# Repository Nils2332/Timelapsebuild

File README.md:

# 3 Axis Camera Motion System

A simple 4 digit stopwatch triggered by 2 remote Buttons<br />

<br />
Demo of Moving System<br />
<br />
Motion-System<br />
<br />
Remote-Controller<br />
## Built With
Motor Driver Board with STM32 Microcontroller and TMC2130 Stepper-Driver.<br />
Remote-Controller with STM32 $\muC
$ Touchscreen and two Joysticks.<br />
Both connected remotly via nRF905 wireless Chip on 868 MHz band. <br />

## License

This project is licensed under the MIT License

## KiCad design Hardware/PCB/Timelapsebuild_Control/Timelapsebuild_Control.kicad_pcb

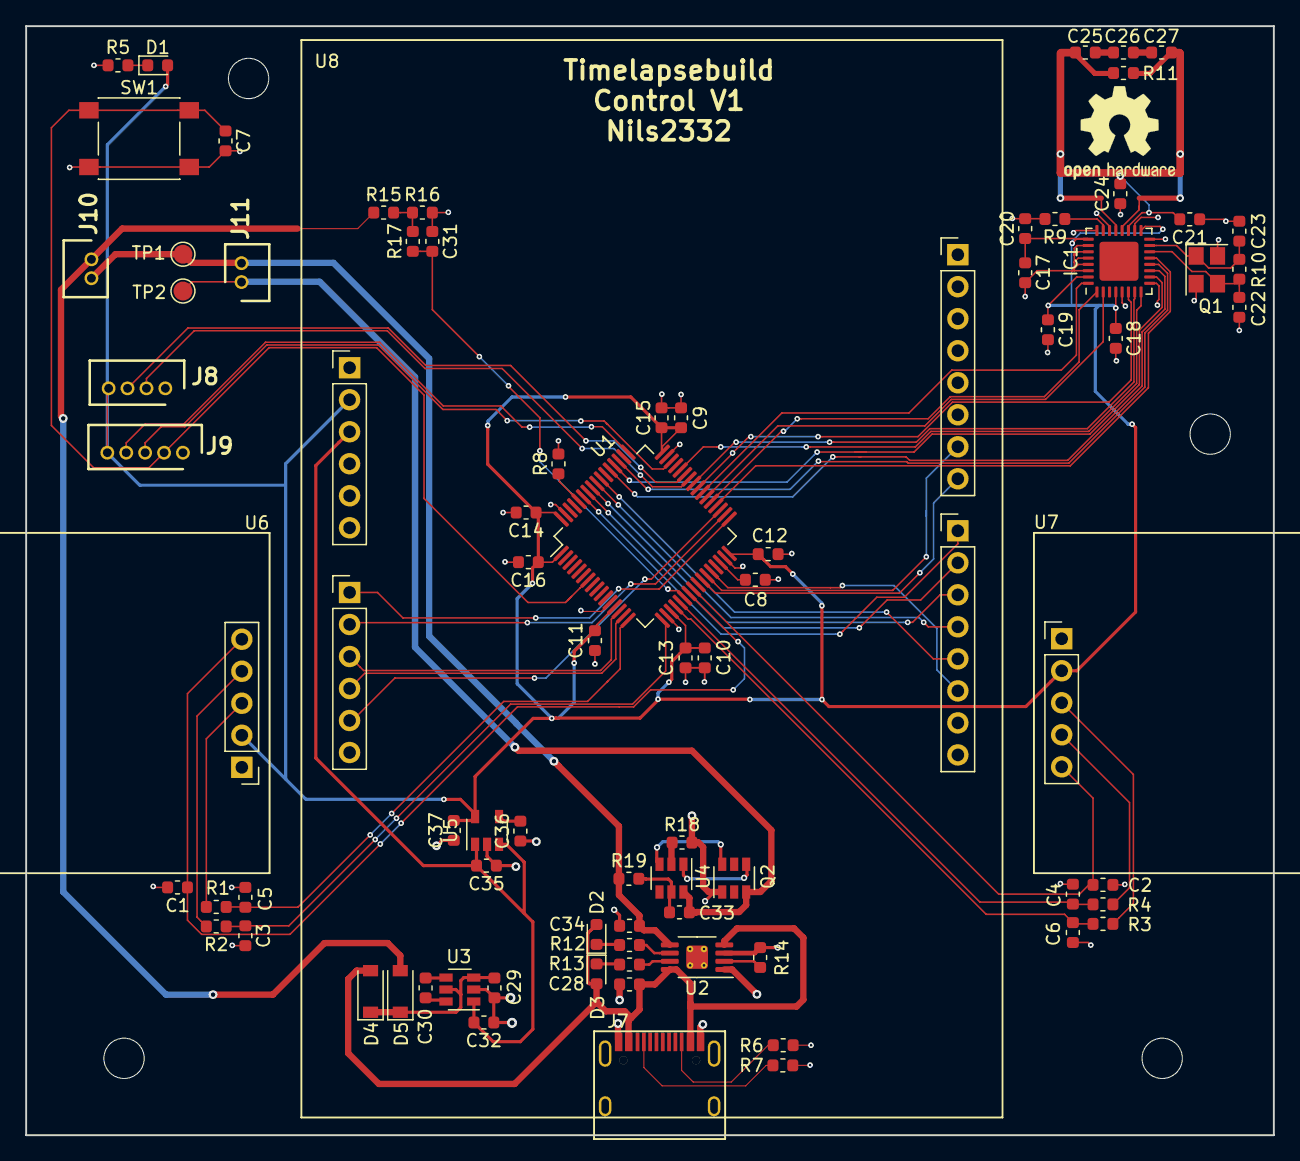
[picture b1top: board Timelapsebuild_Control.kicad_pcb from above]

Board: 2 copper layers, 99.0 x 88.0 mm, 80 parts (0 on the bottom side), 71 nets.

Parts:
C1, C2, C7, C9, C10, C11, C12, C13, C14, C15, C28, C33: 100n; C_0603_1608Metric
C3, C4, C5, C6, C36: 10n; C_0603_1608Metric
C8, C16: 4.7u; C_0603_1608Metric
C17, C18, C24: 33pF; C_0603_1608Metric
C19, C31: 10nF; C_0603_1608Metric
C20: 4.7uF; C_0603_1608Metric
C21: 3.3n; C_0603_1608Metric
C22, C23: 22pF; C_0603_1608Metric
C25: 5.6pF; C_0603_1608Metric
C26: 4.7pF; C_0603_1608Metric
C27: 3.9pF; C_0603_1608Metric
C29, C30, C32, C34: 10uF; C_0603_1608Metric
C35, C37: 1u; C_0603_1608Metric
D1, D2, D3: LED; LED_0603_1608Metric
D4, D5: 1N5819; D_SOD-123
IC1: nRF905; QFN-32-1EP_5x5mm_P0.5mm_EP3.1x3.1mm
J7: USB_C_Receptacle_USB2.0; USB_C_SIMPLE
J8: UART; JST_ZH_B4B_1x04_P1.5mm
J9: ST-Link; JST_ZH_B5B_1x05_P1.5mm
J10: PWR_Con; JST_ZH_B2B_1x02_P1.5mm
J11: Bat Con; JST_ZH_B2B_1x02_P1.5mm
Q1: X322516MRB4SI; Crystal_SMD_3225-4Pin_3.2x2.5mm
Q2: FS8205; SOT-23-6
R1, R2, R3, R4, R8, R17: 10k; R_0603_1608Metric
R5, R12, R13, R18: 1k; R_0603_1608Metric
R6, R7: 5k1; R_0603_1608Metric
R9: 22k; R_0603_1608Metric
R10: 1M; R_0603_1608Metric
R11: 18k; R_0603_1608Metric
R14: 1.2k; R_0603_1608Metric
R15: 400k; R_0603_1608Metric
R16: 100k; R_0603_1608Metric
R19: 100; R_0603_1608Metric
SW1: SW_DIP_x01; SW_SPST_PTS645
TP1, TP2: TestPoint; TestPoint_Pad_D1.5mm
U1: STM32F401RETx; LQFP-64_10x10mm_P0.5mm
U2: TP4056; MSOP-8-1EP_3x3mm_P0.65mm_EP1.73x1.85mm_ThermalVias
U3: HX4004A; SOT-23-6
U4: DW01A; SOT-23-6
U5: SGM2019-3.3YN; SOT-23-5
U6, U7: Joycon
U8: Kuman3.5T-Screen; Kuman 3.5 Display

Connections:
+3V3: C9.1, C10.1, C11.1, C12.1, C13.1, C14.1, C15.1, C16.1, C17.1, C18.1, C19.1, C20.1, C37.2, D1.2, IC1.4, IC1.17, IC1.25, IC1.31, J8.4, J9.5, U1.1, U1.13, U1.19, U1.32, U1.48, U1.64, U5.5, U6.2, U7.2, U8.24
+5V: C32.2, C35.2, U3.1, U5.1, U5.3, U8.25
+5VA: C28.1, D2.2, D3.2, D4.2, J7.A4, J7.A9, J7.B4, J7.B9, U2.4, U2.8
+BATT: C34.1, J10.2, J11.2, R19.1, TP1.1, U2.5
-BATT: C33.2, J11.1, Q2.3, TP2.1, U4.6
/Joycon1-1: C5.1, R1.1, U1.16
/Joycon1-2: C3.1, R2.1, U1.17
/Joycon1-But: C1.1, U1.23, U6.5
/Joycon2-1: C6.1, R3.1, U1.20
/Joycon2-2: C4.1, R4.1, U1.21
/Joycon2-But: C2.1, U1.24, U7.5
/LCD_CS: U1.15, U8.20
/LCD_D0: U1.26, U8.8
/LCD_D1: U1.27, U8.7
/LCD_D2: U1.28, U8.14
/LCD_D3: U1.55, U8.13
/LCD_D4: U1.56, U8.12
/LCD_D5: U1.57, U8.11
/LCD_D6: U1.58, U8.10
/LCD_D7: U1.59, U8.9
/LCD_RD: U1.33, U8.17
/LCD_RS: U1.14, U8.19
/LCD_RST: U1.35, U8.21
/LCD_WR: U1.34, U8.18
/NRST: C7.1, J9.2, SW1.1, U1.7
/SWCLK: J9.4, U1.49
/SWDIO: J9.3, U1.46
/USART1_RX: J8.3, U1.43
/USART1_TX: J8.2, U1.42
Bat_V: C31.2, R17.1, U1.22
CSN: IC1.13, U1.36
DR: IC1.8, U1.44
GND: C1.2, C2.2, C3.2, C4.2, C5.2, C6.2, C7.2, C8.2, C9.2, C10.2, C11.2, C12.2, C13.2, C14.2, C15.2, C16.2, C17.2, C18.2, C19.2, C20.2, C21.1, C22.1, C23.1, C24.1, C28.2, C29.1, C31.1, C32.1, C34.2, C35.1, C36.1, C37.1, IC1.5, IC1.9, IC1.16, IC1.18, IC1.22, IC1.24, IC1.26, IC1.27, IC1.28, IC1.29, IC1.30, J7.A1, J7.A12, J7.B1, J7.B12, J7.S1, J8.1, J9.1, Q1.2, Q1.4, Q2.1, R5.1, R6.2, R7.2, R8.2, R9.2, R14.2, R16.2, R18.2, SW1.2, U1.12, U1.18, U1.31, U1.47, U1.63, U2.1, U2.3, U3.2, U5.2, U6.1, U7.1, U8.26, U8.27
MISO: IC1.10, U1.52
MOSI: IC1.11, U1.53
unnamed: C8.1, U1.30
unnamed: C21.2, C24.2, C25.2, C27.1, IC1.19, IC1.20, IC1.21, R11.1, R11.2
unnamed: C22.2, IC1.14, Q1.3, R10.1
unnamed: C23.2, IC1.15, Q1.1, R10.2
unnamed: C25.1, C26.2
unnamed: C26.1, C27.2
unnamed: C29.2, D4.1, D5.1, U3.3, U3.5
unnamed: C30.1, U3.6
unnamed: C30.2, U3.4
unnamed: C33.1, R19.2, U4.5
unnamed: C36.2, U5.4
unnamed: D1.1, R5.2
unnamed: D2.1, R12.2
unnamed: D3.1, R13.2
unnamed: D5.2, J10.1, R15.1
unnamed: IC1.23, R9.1
unnamed: J7.A5, R7.1
unnamed: J7.B5, R6.1
unnamed: Q2.4, U4.1
unnamed: Q2.6, U4.3
unnamed: R1.2, U6.3
unnamed: R2.2, U6.4
unnamed: R3.2, U7.3
unnamed: R4.2, U7.4
unnamed: R8.1, U1.60
unnamed: R12.1, U2.6
unnamed: R13.1, U2.7
unnamed: R14.1, U2.2
unnamed: R15.2, R16.1, R17.2
unnamed: R18.1, U4.2
PWRUP: IC1.2, U1.38
RF_AM: IC1.7, U1.41
RF_CD: IC1.6, U1.40
SCK: IC1.12, U1.51
TRX_CE: IC1.1, U1.37
TX_EN: IC1.32, U1.39

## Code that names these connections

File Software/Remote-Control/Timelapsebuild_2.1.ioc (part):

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Mcu.Name=STM32F401R(D-E)Tx
Mcu.Package=LQFP64
Mcu.UserName=STM32F401RETx
PA0-WKUP.GPIOParameters=GPIO_PuPd,GPIO_Label
PA0-WKUP.GPIO_Label=LCD_CD
PA0-WKUP.GPIO_PuPd=GPIO_PULLUP
PA0-WKUP.Signal=GPIO_Output
PA1.GPIOParameters=GPIO_PuPd,GPIO_Label
PA1.GPIO_Label=LCD_CS
PA1.GPIO_PuPd=GPIO_PULLUP
PA1.Signal=GPIO_Output
PA10.Mode=Asynchronous
PA10.Signal=USART1_RX
PA11.GPIOParameters=GPIO_Label
PA11.GPIO_Label=DR
PA11.Signal=GPIO_Input
PA13.Mode=Serial_Wire
PA13.Signal=SYS_JTMS-SWDIO
PA14.Mode=Serial_Wire
PA14.Signal=SYS_JTCK-SWCLK
PA2.GPIOParameters=GPIO_Label
PA2.GPIO_Label=Joycon1-1
PA2.Signal=ADCx_IN2
PA3.GPIOParameters=GPIO_Label
PA3.GPIO_Label=Joycon1-2
PA3.Signal=ADCx_IN3
PA4.GPIOParameters=GPIO_Label
PA4.GPIO_Label=Joycon2-1
PA4.Signal=ADCx_IN4
PA5.GPIOParameters=GPIO_Label
PA5.GPIO_Label=Joycon2-2
PA5.Signal=ADCx_IN5
PA6.GPIOParameters=GPIO_Label
PA6.GPIO_Label=Bat
PA6.Signal=ADCx_IN6
PA7.GPIOParameters=GPIO_PuPd,GPIO_Label,GPIO_ModeDefaultEXTI
PA7.GPIO_Label=Joycon1-But
PA7.GPIO_ModeDefaultEXTI=GPIO_MODE_IT_FALLING
PA7.GPIO_PuPd=GPIO_PULLUP
PA7.Signal=GPXTI7
PA8.GPIOParameters=GPIO_Label
PA8.GPIO_Label=RF_AM
PA8.Signal=GPIO_Input
PA9.Mode=Asynchronous
PA9.Signal=USART1_TX
PB0.GPIOParameters=GPIO_Label
PB0.GPIO_Label=LCD_D0
PB0.Signal=GPIO_Input
PB1.GPIOParameters=GPIO_Label
PB1.GPIO_Label=LCD_D1
PB1.Signal=GPIO_Input
PB12.GPIOParameters=GPIO_PuPd,GPIO_Label
PB12.GPIO_Label=LCD_RD
PB12.GPIO_PuPd=GPIO_PULLUP
PB12.Signal=GPIO_Output
PB13.GPIOParameters=GPIO_PuPd,GPIO_Label
PB13.GPIO_Label=LCD_WR
PB13.GPIO_PuPd=GPIO_PULLUP
PB13.Signal=GPIO_Output
PB14.GPIOParameters=GPIO_PuPd,GPIO_Label
PB14.GPIO_Label=LCD_RST
PB14.GPIO_PuPd=GPIO_PULLUP
PB14.Signal=GPIO_Output
PB15.GPIOParameters=PinState,GPIO_Label
PB15.GPIO_Label=CSN
PB15.PinState=GPIO_PIN_SET
PB15.Signal=GPIO_Output
PB2.GPIOParameters=GPIO_Label
PB2.GPIO_Label=LCD_D2
PB2.Signal=GPIO_Input
PB3.GPIOParameters=GPIO_Label
PB3.GPIO_Label=LCD_D3
PB3.Signal=GPIO_Input
PB4.GPIOParameters=GPIO_Label
PB4.GPIO_Label=LCD_D4
PB4.Signal=GPIO_Input
PB5.GPIOParameters=GPIO_Label
PB5.GPIO_Label=LCD_D5
PB5.Signal=GPIO_Input
PB6.GPIOParameters=GPIO_Label
PB6.GPIO_Label=LCD_D6
PB6.Signal=GPIO_Input
PB7.GPIOParameters=GPIO_Label
PB7.GPIO_Label=LCD_D7
PB7.Signal=GPIO_Input
PC10.Mode=Full_Duplex_Master
PC10.Signal=SPI3_SCK
PC11.Mode=Full_Duplex_Master
PC11.Signal=SPI3_MISO
PC12.Mode=Full_Duplex_Master
PC12.Signal=SPI3_MOSI
PC4.GPIOParameters=GPIO_PuPd,GPIO_Label,GPIO_ModeDefaultEXTI
PC4.GPIO_Label=Joycon2-But
PC4.GPIO_ModeDefaultEXTI=GPIO_MODE_IT_FALLING
PC4.GPIO_PuPd=GPIO_PULLUP
PC4.Signal=GPXTI4
PC6.GPIOParameters=GPIO_Label
PC6.GPIO_Label=TRX_CE
PC6.Signal=GPIO_Output
PC7.GPIOParameters=GPIO_Label
PC7.GPIO_Label=PWRUP
PC7.Signal=GPIO_Output
PC8.GPIOParameters=GPIO_Label
PC8.GPIO_Label=TX_EN
PC8.Signal=GPIO_Output
PC9.GPIOParameters=GPIO_Label
PC9.GPIO_Label=RF_CD
PC9.Signal=GPIO_Input
RCC.HSE_VALUE=25000000
RCC.SYSCLKFreq_VALUE=84000000
RCC.SYSCLKSource=RCC_SYSCLKSOURCE_PLLCLK
board=custom

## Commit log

2019-07-31 init
2019-07-31 init2
2019-07-31 CAD-INIT
2019-08-08 sort
2019-08-09 Pictures
